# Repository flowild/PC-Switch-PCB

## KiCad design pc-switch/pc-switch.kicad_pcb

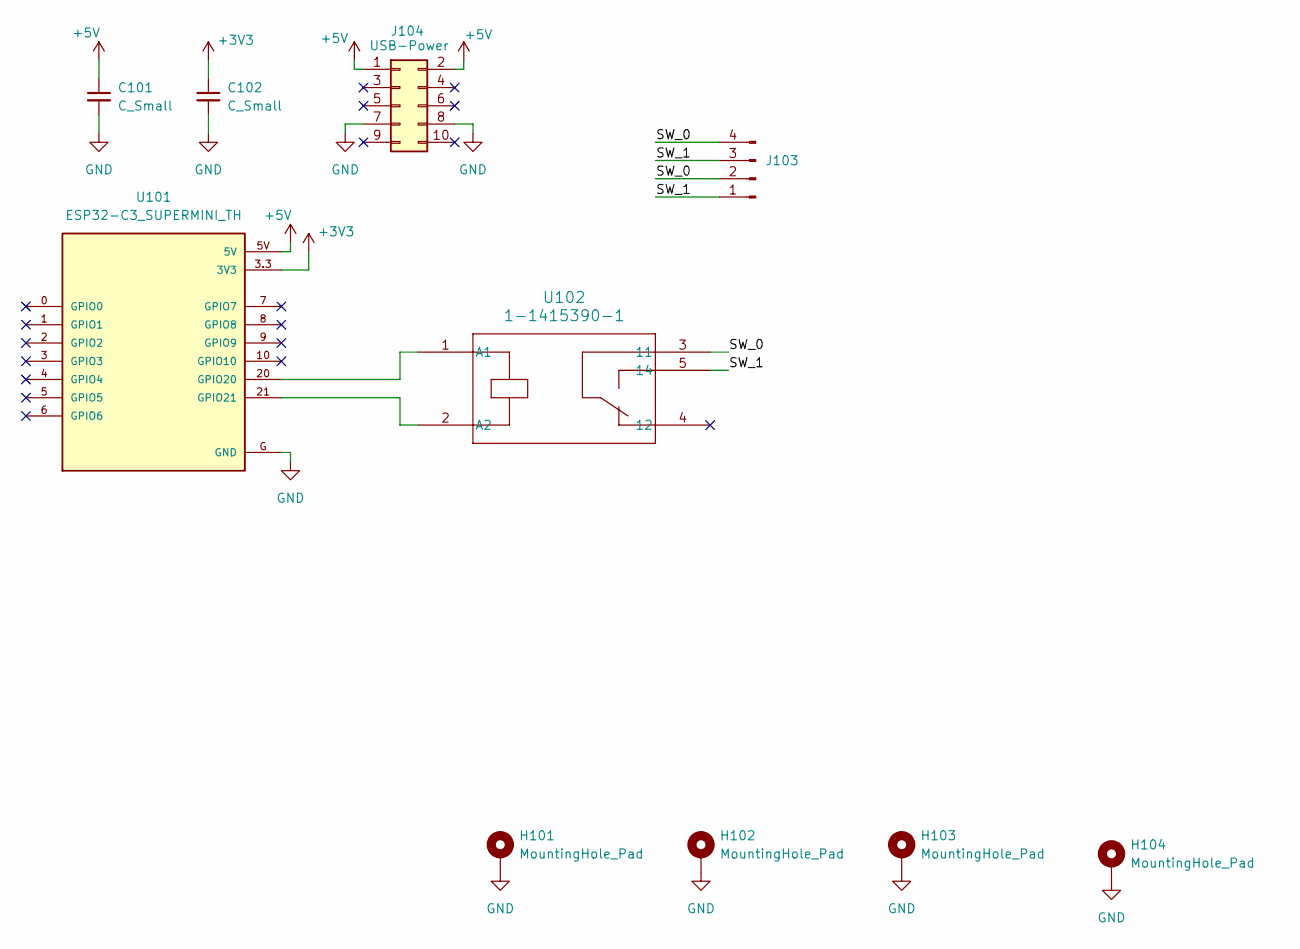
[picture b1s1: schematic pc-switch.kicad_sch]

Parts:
C101, C102: C_Small; C_0805_2012Metric_Pad1.18x1.45mm_HandSolder
H101, H102, H103, H104: MountingHole_Pad; MountingHole_3.2mm_M3_DIN965_Pad
J103: Conn_01x04_Pin; PinHeader_1x04_P2.54mm_Vertical
J104: USB-Power; PinHeader_2x05_P2.54mm_Vertical
U101: ESP32-C3_SUPERMINI_TH; MODULE_ESP32-C3_SUPERMINI_TH
U102: 1-1415390-1; RELAY5_1-1415390-1_TEC

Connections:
+3V3: C102.1, U101.3.3 (3V3)
+5V: C101.1, J104.1, J104.2, U101.5V
/SW_0: J103.2, J103.4, U102.3 (11)
/SW_1: J103.1, J103.3, U102.5 (14)
GND: C101.2, C102.2, H101.1, H102.1, H103.1, H104.1, J104.7, J104.8, U101.G (GND)
unnamed: U101.20 (GPIO20), U102.1 (A1)
unnamed: U101.21 (GPIO21), U102.2 (A2)

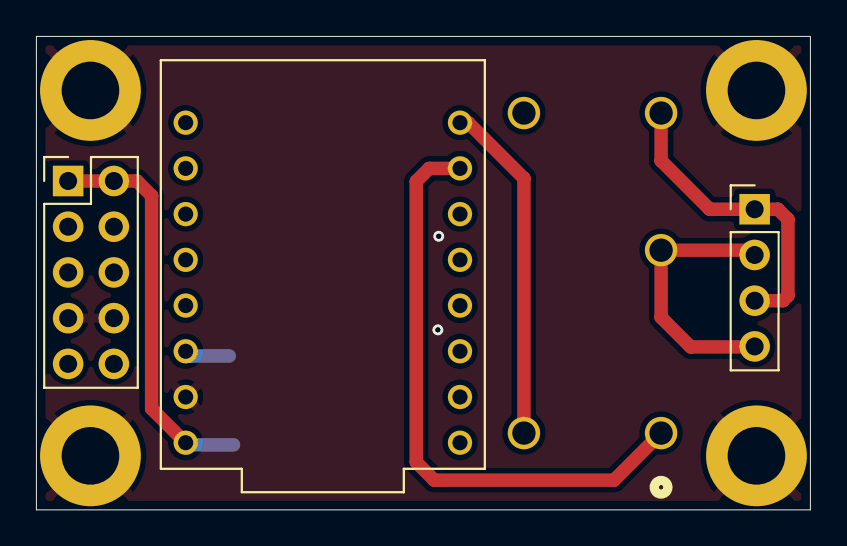
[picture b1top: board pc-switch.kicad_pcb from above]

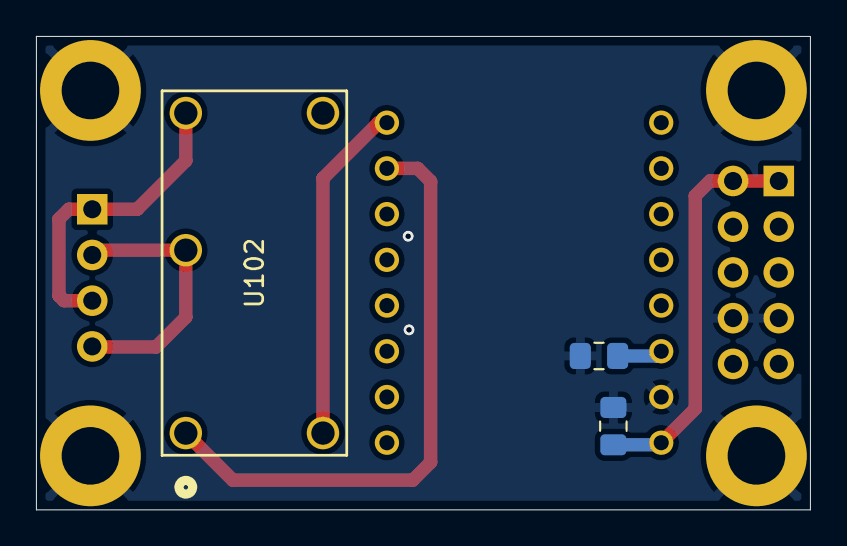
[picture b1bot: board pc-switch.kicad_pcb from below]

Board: 2 copper layers, 43.0 x 26.3 mm, 10 parts (3 on the bottom side), 7 nets.

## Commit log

2025-07-05 Add initial KiCad project files for pc-switch
    Added base schematic (.kicad_sch), PCB layout (.kicad_pcb), and project configuration (.kicad_pro) files for the new pc-switch hardware project. These files establish the initial structure for furthe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
2025-07-05 Update README with installation instructions
    Added a new section to the README file detailing the steps required to install the project dependencies and set up the development environment.
2025-07-06 Add new feature to process user input
    Implemented a function to handle and validate user input in the main application module. This improves input reliability and prepares the codebase for future enhancements.
2025-07-09 deleting some files
